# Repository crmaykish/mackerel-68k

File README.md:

# Mackerel 68k

Mackerel 68k is a family of homebrew single-board computers built around the Motorola 68000 line of processors plus a from-scratch effort to run **mainline Linux** on each one.

The project works its way up the 68k family one chip at a time, from the 68008 to the 68040. Each new board adds capability: more memory, faster CPUs, an FPU, an MMU, and richer peripherals. But the throughline is software - every Mackerel runs the **latest mainline Linux kernel**, from a tiny NOMMU uClinux shell on the 68008 up to a full MMU + hardware-FPU install on the 68030.

What's in the box, top to bottom:

- **Bespoke hardware** - custom PCBs with programmable logic chips (22V10 GALs on the 68008, Altera CPLDs on the later boards) handling address decoding, DRAM control, and interrupts.
- **A homegrown bootloader** - a small ROM monitor on every board with debug tools (peek, poke, memtest), YMODEM file transfer, and the ability to boot Linux from IDE or SD.
- **Custom toolchains** - bare-metal and Linux (MMU + NOMMU) GCC cross-compilers built with crosstool-ng.
- **Mainline Linux** - kernel port with drivers for the DUART, IDE storage, and Ethernet-over-SPI, booting to a BusyBox userspace.
- **Fully open source** - every schematic, PCB layout, logic file, and line of code is open, and hobbyists around the world have built their own Mackerel boards.

Three discrete boards are running today (68008, 68010, and 68030), with a 68040 system in the works - plus Mackerel-F, an FPGA build that runs a full Mackerel system on a soft 68000 core.

## Links

1. [Hackaday Project Page](https://hackaday.io/project/183861-mackerel-68k-computer)
2. [Mackerel Linux v7.1.x](https://github.com/crmaykish/mackerel-linux/tree/mackerel)
3. [Mackerel uClinux (deprecated)](https://github.com/crmaykish/mackerel-uclinux-20160919)

## Docs

1. [Mackerel-08 Assembly](docs/mackerel-08-board-assembly.md)
2. [How to Compile Code and Programmable Logic](docs/how-to-compile-everything.md)
3. [Building the Mackerel Toolchains](docs/building-the-mackerel-toolchains.md)
4. [Building and Booting Linux on Mackerel](docs/building-linux-for-mackerel.md)
5. [Building and Running Mackerel-F (FPGA)](docs/building-and-running-mackerel-f.md)

## Hardware

### Mackerel-08

Status: Complete

- MC68008 CPU (52-pin PLCC variant)
- 512 KB of Flash ROM, 3.5MB SRAM
- Two serial ports
- SD card support (bitbang SPI)
- Linux 7.1.x NOMMU

Based on the original prototype hardware, this SBC combines the 52-pin PLCC MC68008, a 512KB Flash ROM, up to 3.5MB of SRAM, and a XR68C681 DUART on a single PCB. The DUART exposes two serial ports and three bit-banged SPI headers. One of these headers is currently used with an SD card breakout board to provide bulk storage.

Three 22V10 PLDs are used for address decoding, interrupt mapping, and DTACK generation. An expansion header breaks out address, data, and control lines to allow additional peripherals to be connected directly to the processor bus.

The address space is mapped as follows:

- RAM:    0x000000 - 0x37FFFF (up to 3.5 MB)
- ROM:    0x380000 - 0x3FBFFF (496/512 KB usable)
- DUART:  0x3FC000 - 0x3FDFFF (8KB)
- Exp:    0x3FE000 - 0x3FFFFF (Expansion header, 8KB)

Mackerel-08 uses a 74HC595 shift register to create a BOOT signal for the first eight /AS cycles of the CPU after reset. This BOOT signal is used by the address decoder PLD to map the ROM to address 0x000000 long enough for the CPU to read the initial stack pointer and program counter vectors from ROM. RAM is mapped to 0x000000 after that.

### Mackerel-10

Status: Complete

- MC68000 or MC68010 CPU
- 1 MB of ROM, 1 MB of SRAM
- Up to 16 MB of 30-pin DRAM (15 usable)
- Two serial ports
- IDE interface
- Linux 7.1.x NOMMU

Mackerel-10 is the second SBC in the project. It expands on the design of Mackerel-08 with a MC68010 CPU (or equivalent), the same XR68C681 DUART, 1MB of Flash ROM, 1MB of SRAM, up to 16 MB of DRAM, and an IDE drive interface. Two CPLDs act as the glue logic and DRAM controller for the board. The SRAM is optional and the address space can be filled almost entirely with DRAM.

The memory map looks like this:

- DRAM:     0x000000 - 0xDFFFFF (14MB)
- SRAM:     0xE00000 - 0xEFFFFF (1 MB)
- ROM:      0xF00000 - 0xFF4000 (not quite 1MB)
- I/O:      0xF40000 - 0xFFFFFF

It's also possible to install a MC68SEC000 CPU on [an adapter](https://github.com/crmaykish/adapters-and-breakout-boards/tree/main/MC68SEC000-to-DIP-64) for a major speed boost. This CPU can run at 33 MHz with the correct CPU oscillator installed and an updated system controller CPLD.

### Mackerel-30

Status: Prototype

- MC68030 CPU at 20 MHz
- MC68882 FPU
- 512 KB ROM, 512 KB SRAM
- 128 MB of 72-pin DRAM
- Two serial ports
- IDE interface
- Ethernet over SPI
- Linux 7.1.x

Mackerel-30 is based on the 68030 CPU. It includes the DUART and IDE interface from Mackerel-10 and upgrades the DRAM controller to use a 72-pin SIMM. It also includes a MC68882 FPU.

### Mackerel-40
Status: Design

- 68040 CPU at 33 MHz (internal MMU and FPU)
- 2 MB of ROM, 2 MB SRAM
- 2x72 pin SIMMs (up to 256 MB of DRAM)
- Dedicated I/O controller (SPI, I2C, GPIO)
- DUART and IDE from earlier boards

### Mackerel-F

Status: Prototype (FPGA)

- fx68k soft 68000 core at 37.8 MHz, in a Tang Nano 20k
- 8 MB SDRAM
- 30 KB ROM (bootloader) and 32 KB BSRAM
- UART console, programmable timer, and interrupt controller
- microSD (SPI) and W5500 Ethernet
- Linux 7.1.x NOMMU

Mackerel-F is an entire Mackerel system implemented inside an FPGA. Everything that is discrete hardware on the other boards - the CPU, glue logic, memory controller, UART, timer, interrupt controller, and SPI masters - is RTL here, built around the [fx68k](https://github.com/ijor/fx68k) soft 68000 core and synthesized for the Tang Nano 20k. The SoC runs at 75.6 MHz with the 68000 core clocked at half that (37.8 MHz).

Unlike the other boards there is no separate ROM chip: the bootloader is baked into the FPGA bitstream as on-chip ROM and its scratch RAM lives in block RAM, so the entire 8 MB of SDRAM is free for Linux. Alongside the usual `boot` (from SD) and YMODEM transfer, the bootloader adds a `netboot` command that pulls the kernel over Ethernet (raw TCP, with a small host server) and a five-second SD autoboot.

The memory map:

- RAM:    0x000000 - 0x7FFFFF (8 MB SDRAM, the top 384 KB holds the execute-in-place root filesystem)
- BSRAM:  0xFF0000 - 0xFF7FFF (32 KB, bootloader RAM)
- ROM:    0xFF8000 - 0xFFF7FF (30 KB, bootloader ROM)
- I/O:    0xFFF800 - 0xFFFFFF (GPIO, UART, timer, two SPI masters, interrupt controller)

It boots mainline NOMMU uClinux to a BusyBox shell from a ROMfs root run in place from SDRAM, with the microSD for storage and the W5500 for networking. See [Building and Running Mackerel-F (FPGA)](docs/building-and-running-mackerel-f.md).

## Software

### Bootloader and Bare-metal Programs
Every version of Mackerel runs a small bootloader program installed on the Flash ROM. This provides a simple set of debugging tools (peek, poke, memtest, etc.) as well as two methods for loading external code.

The bootloader supports the YMODEM protocol for loading programs and data into RAM (see the `ymodem` command), using `lrzsz-sb` on the PC for example. Other terminal programs like TeraTerm should also work.

The `boot` command is used to load the Linux kernel from disk (SD or IDE). It expects a `IMAGE.BIN` file on the first FAT16 partition of the drive. See the `prepare_disk.sh` script in the [mackerel-linux repository](https://github.com/crmaykish/mackerel-linux).

On Mackerel-F the bootloader also supports `netboot` (pulling the kernel over Ethernet) and a five-second SD autoboot on power-up.

### Linux on Mackerel

Every Mackerel board runs the latest mainline kernel (v7.1.x). Mackerel-08, Mackerel-10, and the FPGA-based Mackerel-F run NOMMU and are more limited in their capabilities. Mackerel-30 supports the MMU and the external FPU in Linux and functions more like a traditional headless Linux install. Userspace is made up of busybox (init and shell) with driver support for the DUART, IDE storage, and networking over SPI.

### Compilers and Tools
There are three different toolchains for Mackerel. The baremetal toolchain builds the bootloader and other low level programs in this repo. There are also two variants of the Linux toolchain - one for Mackerel-30 with MMU support and the other for NOMMU/ucLinux on Mackerel-08/10. Prebuilt toolchains are available on the [releases page](https://github.com/crmaykish/mackerel-68k/releases/tag/toolchains-2026-06-06); see [Building the Mackerel Toolchains](docs/building-the-mackerel-toolchains.md) for both the download steps and instructions on building them all with crosstools-ng.

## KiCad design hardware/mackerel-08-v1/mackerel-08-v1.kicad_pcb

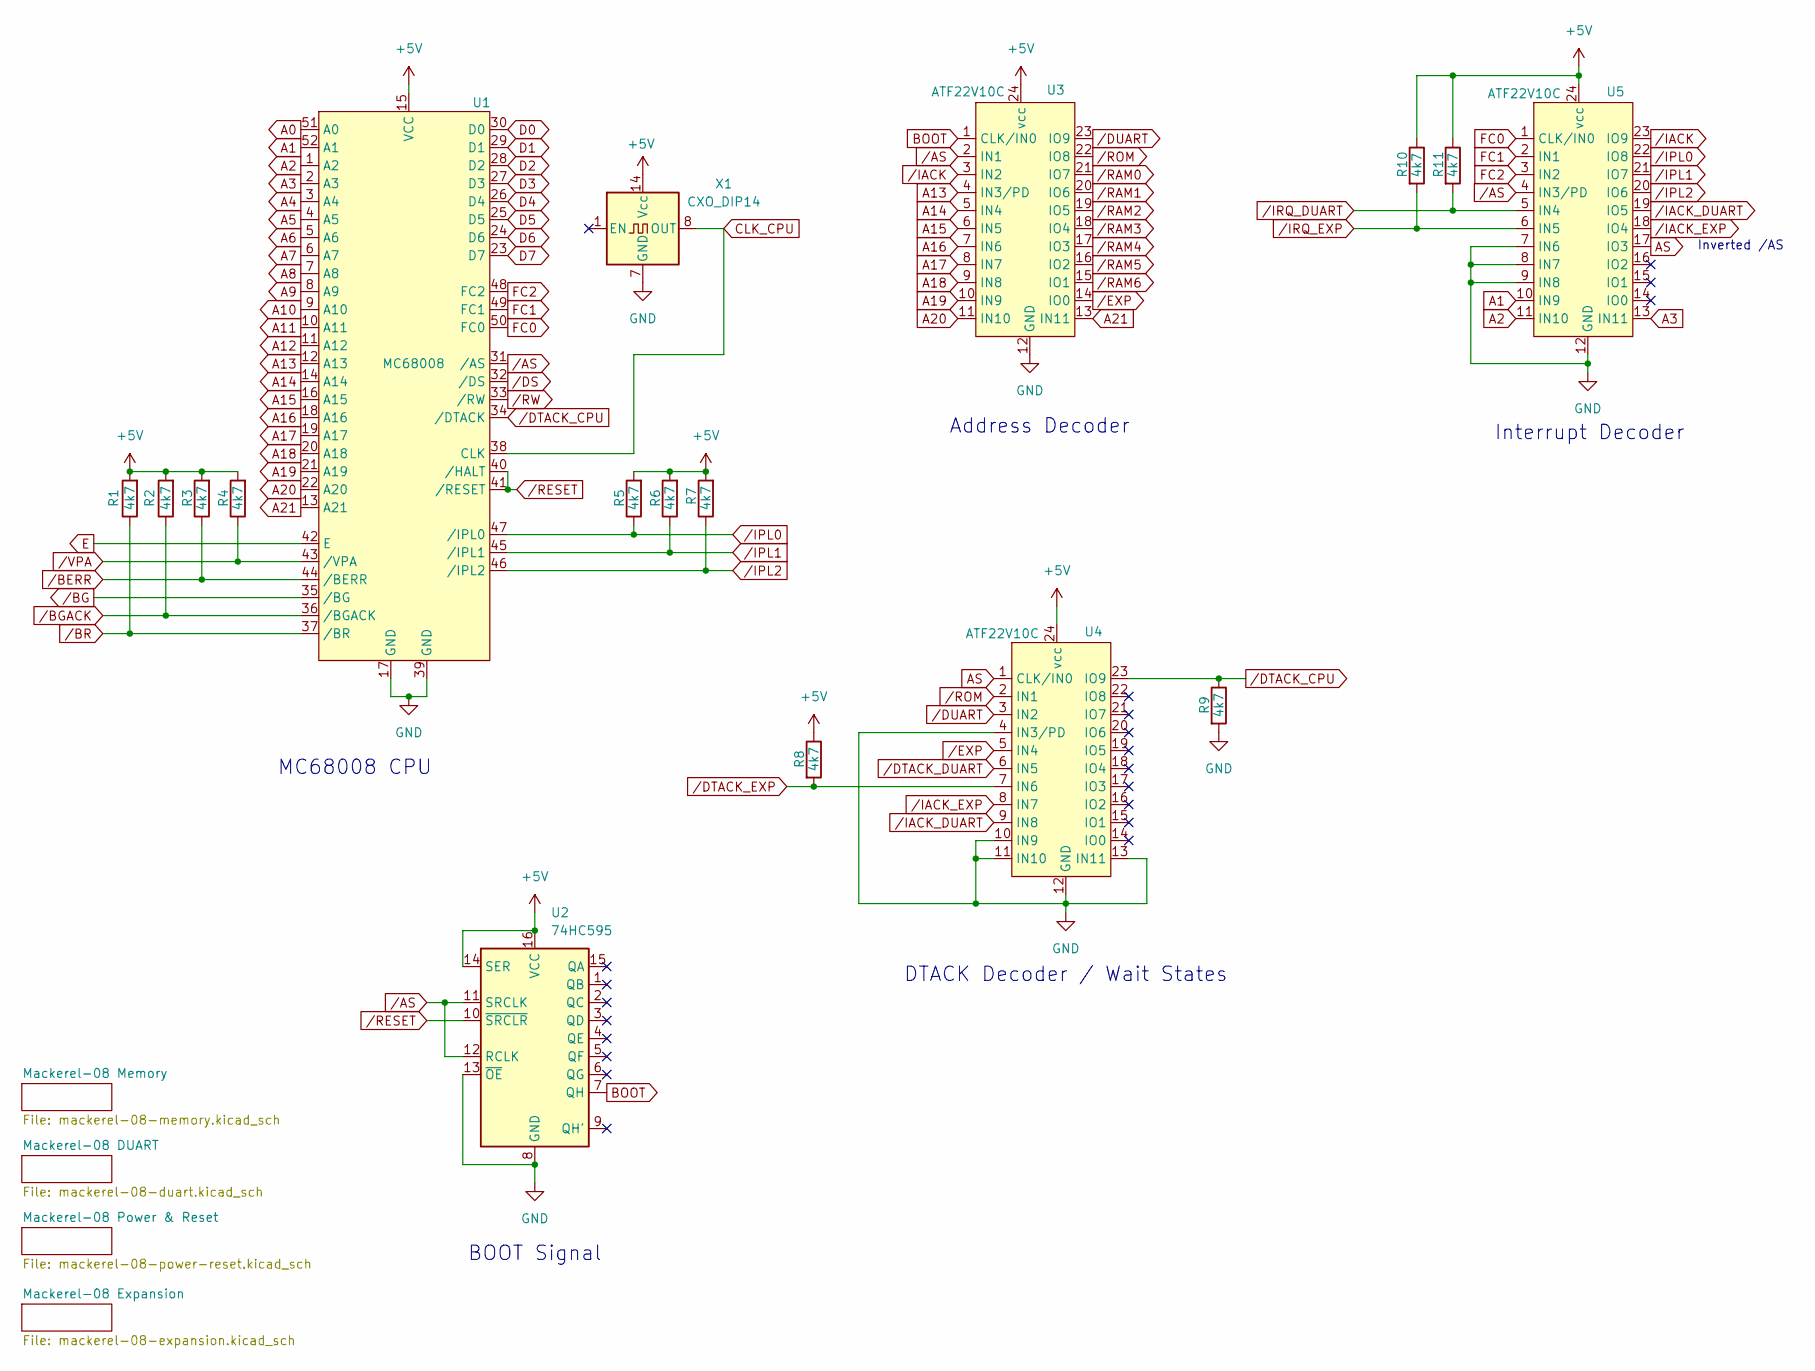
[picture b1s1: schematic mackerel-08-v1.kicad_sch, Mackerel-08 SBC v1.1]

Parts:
R1, R2, R3, R4, R5, R6, R7, R8, R9, R10, R11: 4k7; R_1206_3216Metric_Pad1.30x1.75mm_HandSolder
U1: MC68008; PLCC-52_THT-Socket
U2: 74HC595; DIP-16_W7.62mm
U3, U4, U5: ATF22V10C; DIP-24_W7.62mm
X1: CXO_DIP14; Oscillator_DIP-14

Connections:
+5V: R1.2, R2.2, R3.2, R4.2, R5.2, R6.2, R7.2, R8.1, R10.1, R11.1, U1.15 (VCC), U2.14 (SER), U2.16 (VCC), U3.24 (vcc), U4.24 (vcc), U5.24 (vcc), X1.14 (Vcc); also elsewhere on the board
A0: U1.51 (A0); also elsewhere on the board
A1: U1.52 (A1), U5.10 (IN9); also elsewhere on the board
A2: U1.1 (A2), U5.11 (IN10); also elsewhere on the board
A3: U1.2 (A3), U5.13 (IN11); also elsewhere on the board
A4: U1.3 (A4); also elsewhere on the board
A5: U1.4 (A5); also elsewhere on the board
A6: U1.5 (A6); also elsewhere on the board
A7: U1.6 (A7); also elsewhere on the board
A8: U1.7 (A8); also elsewhere on the board
A9: U1.8 (A9); also elsewhere on the board
A10: U1.9 (A10); also elsewhere on the board
A11: U1.10 (A11); also elsewhere on the board
A12: U1.11 (A12); also elsewhere on the board
A13: U1.12 (A13), U3.4 (IN3/PD); also elsewhere on the board
A14: U1.14 (A14), U3.5 (IN4); also elsewhere on the board
A15: U1.16 (A15), U3.6 (IN5); also elsewhere on the board
A16: U1.18 (A16), U3.7 (IN6); also elsewhere on the board
A17: U1.19 (A17), U3.8 (IN7); also elsewhere on the board
A18: U1.20 (A18), U3.9 (IN8); also elsewhere on the board
A19: U1.21 (A19), U3.10 (IN9); also elsewhere on the board
A20: U1.22 (A20), U3.11 (IN10); also elsewhere on the board
A21: U1.13 (A21), U3.13 (IN11); also elsewhere on the board
AS: U4.1 (CLK/IN0), U5.17 (IO3)
BOOT: U2.7 (QH), U3.1 (CLK/IN0)
CLK_CPU: U1.38 (CLK), X1.8 (OUT); also elsewhere on the board
D0: U1.30 (D0); also elsewhere on the board
D1: U1.29 (D1); also elsewhere on the board
D2: U1.28 (D2); also elsewhere on the board
D3: U1.27 (D3); also elsewhere on the board
D4: U1.26 (D4); also elsewhere on the board
D5: U1.25 (D5); also elsewhere on the board
D6: U1.24 (D6); also elsewhere on the board
D7: U1.23 (D7); also elsewhere on the board
E: U1.42 (E); also elsewhere on the board
FC0: U1.50 (FC0), U5.1 (CLK/IN0)
FC1: U1.49 (FC1), U5.2 (IN1)
FC2: U1.48 (FC2), U5.3 (IN2)
GND: R9.2, U1.17 (GND), U1.39 (GND), U2.8 (GND), U2.13 (~OE), U3.12 (GND), U4.4 (IN3/PD), U4.10 (IN9), U4.11 (IN10), U4.12 (GND), U4.13 (IN11), U5.7 (IN6), U5.8 (IN7), U5.9 (IN8), U5.12 (GND), X1.7 (GND); also elsewhere on the board
/AS: U1.31 (/AS), U2.11 (SRCLK), U2.12 (RCLK), U3.2 (IN1), U5.4 (IN3/PD); also elsewhere on the board
/BERR: R3.1, U1.44 (/BERR); also elsewhere on the board
/BG: U1.35 (/BG); also elsewhere on the board
/BGACK: R2.1, U1.36 (/BGACK); also elsewhere on the board
/BR: R1.1, U1.37 (/BR); also elsewhere on the board
/DS: U1.32 (/DS); also elsewhere on the board
/DTACK_CPU: R9.1, U1.34 (/DTACK), U4.23 (IO9)
/DTACK_DUART: U4.6 (IN5); also elsewhere on the board
/DTACK_EXP: R8.2, U4.7 (IN6); also elsewhere on the board
/DUART: U3.23 (IO9), U4.3 (IN2); also elsewhere on the board
/EXP: U3.14 (IO0), U4.5 (IN4); also elsewhere on the board
/IACK: U3.3 (IN2), U5.23 (IO9)
/IACK_DUART: U4.9 (IN8), U5.19 (IO5); also elsewhere on the board
/IACK_EXP: U4.8 (IN7), U5.18 (IO4); also elsewhere on the board
/IPL0: R5.1, U1.47 (/IPL0), U5.22 (IO8)
/IPL1: R6.1, U1.45 (/IPL1), U5.21 (IO7)
/IPL2: R7.1, U1.46 (/IPL2), U5.20 (IO6)
/IRQ_DUART: R11.2, U5.5 (IN4); also elsewhere on the board
/IRQ_EXP: R10.2, U5.6 (IN5); also elsewhere on the board
/RAM0: U3.21 (IO7); also elsewhere on the board
/RAM1: U3.20 (IO6); also elsewhere on the board
/RAM2: U3.19 (IO5); also elsewhere on the board
/RAM3: U3.18 (IO4); also elsewhere on the board
/RAM4: U3.17 (IO3); also elsewhere on the board
/RAM5: U3.16 (IO2); also elsewhere on the board
/RAM6: U3.15 (IO1); also elsewhere on the board
/RESET: U1.40 (/HALT), U1.41 (/RESET), U2.10 (~SRCLR); also elsewhere on the board
/ROM: U3.22 (IO8), U4.2 (IN1); also elsewhere on the board
/RW: U1.33 (/RW); also elsewhere on the board
/VPA: R4.1, U1.43 (/VPA); also elsewhere on the board

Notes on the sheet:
DTACK Decoder / Wait States
MC68008 CPU
Inverted /AS
BOOT Signal
Interrupt Decoder
Address Decoder

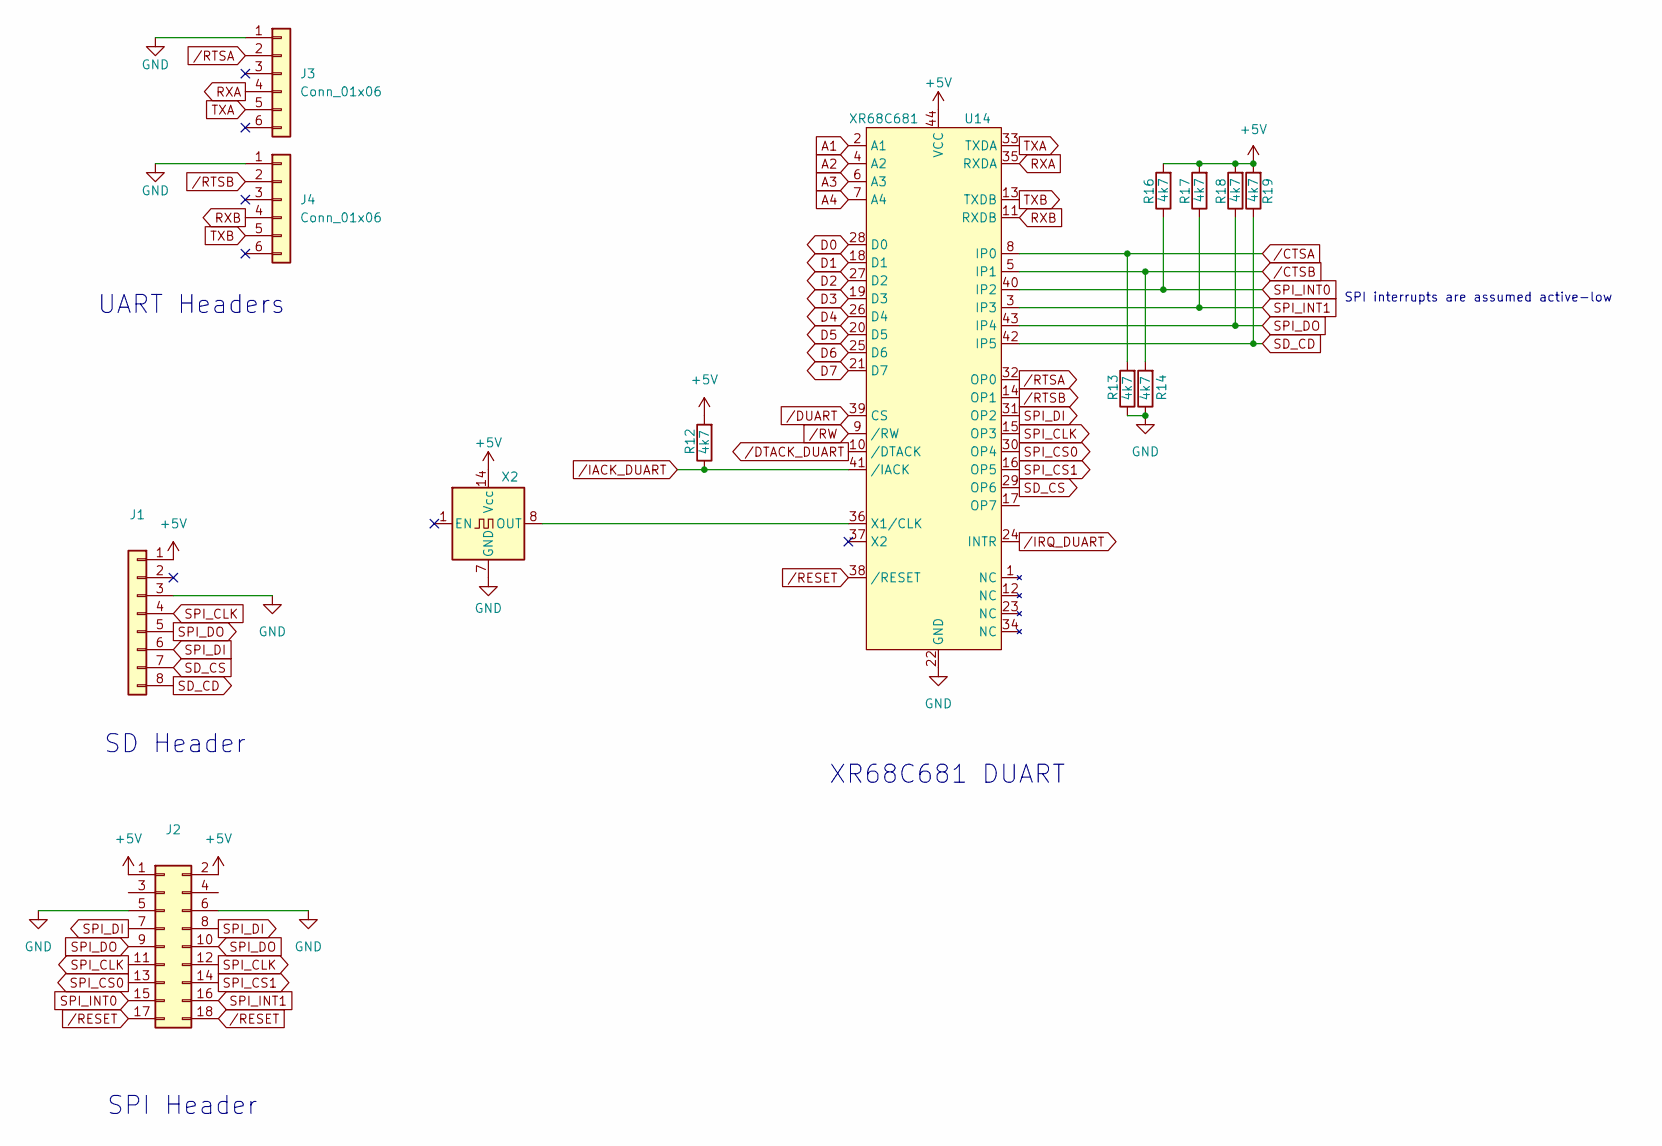
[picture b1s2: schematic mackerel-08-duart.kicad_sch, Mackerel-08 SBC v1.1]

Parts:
J1: Conn_01x08; PinSocket_1x08_P2.54mm_Vertical
J2: Conn_02x09_Odd_Even; PinHeader_2x09_P2.54mm_Vertical
J3, J4: Conn_01x06; PinSocket_1x06_P2.54mm_Horizontal
R12, R13, R14, R16, R17, R18, R19: 4k7; R_1206_3216Metric_Pad1.30x1.75mm_HandSolder
U14: XR68C681; PLCC-44_THT-Socket
X2: CXO_DIP14; Oscillator_DIP-14

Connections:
+5V: J1.1, J2.1, J2.2, R12.2, R16.2, R17.2, R18.2, R19.2, U14.44 (VCC), X2.14 (Vcc); also elsewhere on the board
/Mackerel-08 DUART/USR_LED: U14.17 (OP7); also elsewhere on the board
A1: U14.2 (A1); also elsewhere on the board
A2: U14.4 (A2); also elsewhere on the board
A3: U14.6 (A3); also elsewhere on the board
A4: U14.7 (A4); also elsewhere on the board
D0: U14.28 (D0); also elsewhere on the board
D1: U14.18 (D1); also elsewhere on the board
D2: U14.27 (D2); also elsewhere on the board
D3: U14.19 (D3); also elsewhere on the board
D4: U14.26 (D4); also elsewhere on the board
D5: U14.20 (D5); also elsewhere on the board
D6: U14.25 (D6); also elsewhere on the board
D7: U14.21 (D7); also elsewhere on the board
GND: J1.3, J2.5, J2.6, J3.1, J4.1, R13.1, R14.1, U14.22 (GND), X2.7 (GND); also elsewhere on the board
unnamed: U14.36 (X1/CLK), X2.8 (OUT)
RXA: J3.4, U14.35 (RXDA)
RXB: J4.4, U14.11 (RXDB)
SD_CD: J1.8, R19.1, U14.42 (IP5)
SD_CS: J1.7, U14.29 (OP6)
SPI_CLK: J1.4, J2.11, J2.12, U14.15 (OP3)
SPI_CS0: J2.13, U14.30 (OP4)
SPI_CS1: J2.14, U14.16 (OP5)
SPI_DI: J1.6, J2.7, J2.8, U14.31 (OP2)
SPI_DO: J1.5, J2.9, J2.10, R18.1, U14.43 (IP4)
SPI_INT0: J2.15, R16.1, U14.40 (IP2)
SPI_INT1: J2.16, R17.1, U14.3 (IP3)
TXA: J3.5, U14.33 (TXDA)
TXB: J4.5, U14.13 (TXDB)
/CTSA: R13.2, U14.8 (IP0)
/CTSB: R14.2, U14.5 (IP1)
/DTACK_DUART: U14.10 (/DTACK); also elsewhere on the board
/DUART: U14.39 (CS); also elsewhere on the board
/IACK_DUART: R12.1, U14.41 (/IACK); also elsewhere on the board
/IRQ_DUART: U14.24 (INTR); also elsewhere on the board
/RESET: J2.17, J2.18, U14.38 (/RESET); also elsewhere on the board
/RTSA: J3.2, U14.32 (OP0)
/RTSB: J4.2, U14.14 (OP1)
/RW: U14.9 (/RW); also elsewhere on the board

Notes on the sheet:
SPI interrupts are assumed active-low
XR68C681 DUART
SPI Header
UART Headers
SD Header

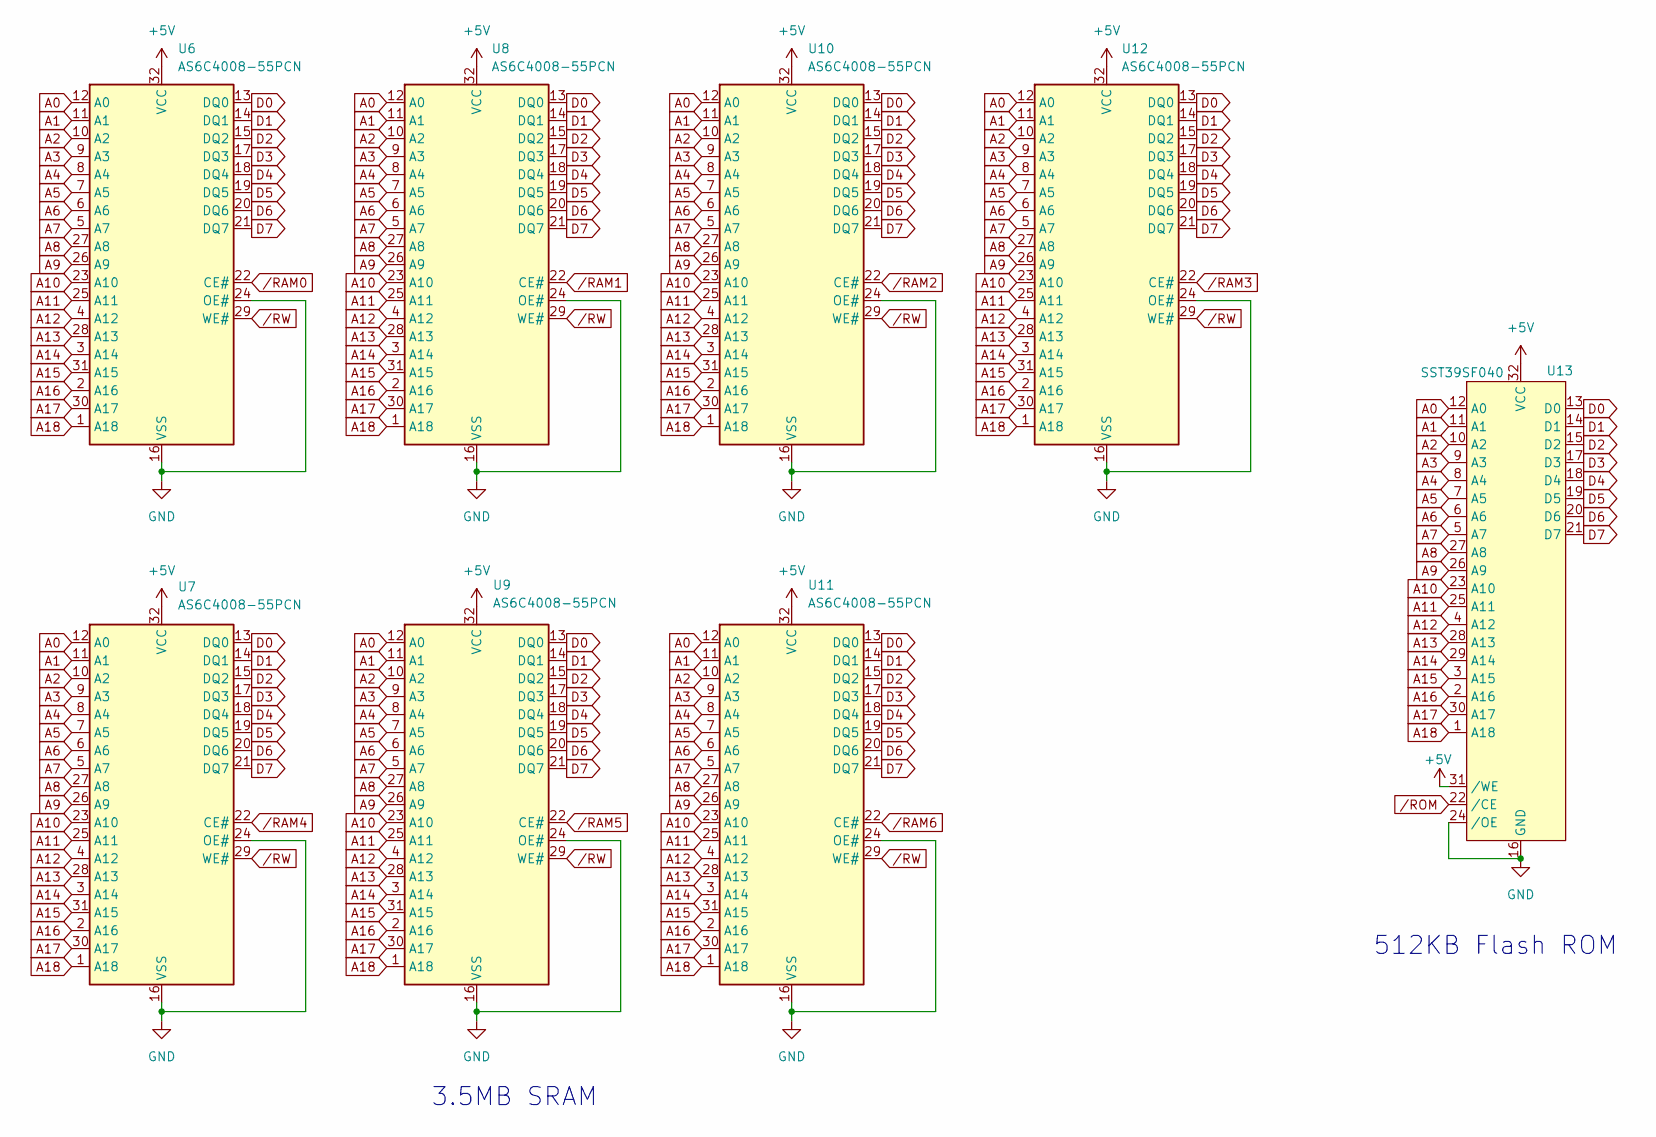
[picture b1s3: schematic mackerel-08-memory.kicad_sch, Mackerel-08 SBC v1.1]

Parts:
U6, U7, U8, U9, U10, U11, U12: AS6C4008-55PCN; DIP-32_W15.24mm
U13: SST39SF040; DIP_Socket-32_W11.9_W12.7_W15.24_W17.78_W18.5_3M_232-1285-0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

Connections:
+5V: U6.32 (VCC), U7.32 (VCC), U8.32 (VCC), U9.32 (VCC), U10.32 (VCC), U11.32 (VCC), U12.32 (VCC), U13.31 (/WE), U13.32 (VCC); also elsewhere on the board
A0: U6.12 (A0), U7.12 (A0), U8.12 (A0), U9.12 (A0), U10.12 (A0), U11.12 (A0), U12.12 (A0), U13.12 (A0); also elsewhere on the board
A1: U6.11 (A1), U7.11 (A1), U8.11 (A1), U9.11 (A1), U10.11 (A1), U11.11 (A1), U12.11 (A1), U13.11 (A1); also elsewhere on the board
A2: U6.10 (A2), U7.10 (A2), U8.10 (A2), U9.10 (A2), U10.10 (A2), U11.10 (A2), U12.10 (A2), U13.10 (A2); also elsewhere on the board
A3: U6.9 (A3), U7.9 (A3), U8.9 (A3), U9.9 (A3), U10.9 (A3), U11.9 (A3), U12.9 (A3), U13.9 (A3); also elsewhere on the board
A4: U6.8 (A4), U7.8 (A4), U8.8 (A4), U9.8 (A4), U10.8 (A4), U11.8 (A4), U12.8 (A4), U13.8 (A4); also elsewhere on the board
A5: U6.7 (A5), U7.7 (A5), U8.7 (A5), U9.7 (A5), U10.7 (A5), U11.7 (A5), U12.7 (A5), U13.7 (A5); also elsewhere on the board
A6: U6.6 (A6), U7.6 (A6), U8.6 (A6), U9.6 (A6), U10.6 (A6), U11.6 (A6), U12.6 (A6), U13.6 (A6); also elsewhere on the board
A7: U6.5 (A7), U7.5 (A7), U8.5 (A7), U9.5 (A7), U10.5 (A7), U11.5 (A7), U12.5 (A7), U13.5 (A7); also elsewhere on the board
A8: U6.27 (A8), U7.27 (A8), U8.27 (A8), U9.27 (A8), U10.27 (A8), U11.27 (A8), U12.27 (A8), U13.27 (A8); also elsewhere on the board
A9: U6.26 (A9), U7.26 (A9), U8.26 (A9), U9.26 (A9), U10.26 (A9), U11.26 (A9), U12.26 (A9), U13.26 (A9); also elsewhere on the board
A10: U6.23 (A10), U7.23 (A10), U8.23 (A10), U9.23 (A10), U10.23 (A10), U11.23 (A10), U12.23 (A10), U13.23 (A10); also elsewhere on the board
A11: U6.25 (A11), U7.25 (A11), U8.25 (A11), U9.25 (A11), U10.25 (A11), U11.25 (A11), U12.25 (A11), U13.25 (A11); also elsewhere on the board
A12: U6.4 (A12), U7.4 (A12), U8.4 (A12), U9.4 (A12), U10.4 (A12), U11.4 (A12), U12.4 (A12), U13.4 (A12); also elsewhere on the board
A13: U6.28 (A13), U7.28 (A13), U8.28 (A13), U9.28 (A13), U10.28 (A13), U11.28 (A13), U12.28 (A13), U13.28 (A13); also elsewhere on the board
A14: U6.3 (A14), U7.3 (A14), U8.3 (A14), U9.3 (A14), U10.3 (A14), U11.3 (A14), U12.3 (A14), U13.29 (A14); also elsewhere on the board
A15: U6.31 (A15), U7.31 (A15), U8.31 (A15), U9.31 (A15), U10.31 (A15), U11.31 (A15), U12.31 (A15), U13.3 (A15); also elsewhere on the board
A16: U6.2 (A16), U7.2 (A16), U8.2 (A16), U9.2 (A16), U10.2 (A16), U11.2 (A16), U12.2 (A16), U13.2 (A16); also elsewhere on the board
A17: U6.30 (A17), U7.30 (A17), U8.30 (A17), U9.30 (A17), U10.30 (A17), U11.30 (A17), U12.30 (A17), U13.30 (A17); also elsewhere on the board
A18: U6.1 (A18), U7.1 (A18), U8.1 (A18), U9.1 (A18), U10.1 (A18), U11.1 (A18), U12.1 (A18), U13.1 (A18); also elsewhere on the board
D0: U6.13 (DQ0), U7.13 (DQ0), U8.13 (DQ0), U9.13 (DQ0), U10.13 (DQ0), U11.13 (DQ0), U12.13 (DQ0), U13.13 (D0); also elsewhere on the board
D1: U6.14 (DQ1), U7.14 (DQ1), U8.14 (DQ1), U9.14 (DQ1), U10.14 (DQ1), U11.14 (DQ1), U12.14 (DQ1), U13.14 (D1); also elsewhere on the board
D2: U6.15 (DQ2), U7.15 (DQ2), U8.15 (DQ2), U9.15 (DQ2), U10.15 (DQ2), U11.15 (DQ2), U12.15 (DQ2), U13.15 (D2); also elsewhere on the board
D3: U6.17 (DQ3), U7.17 (DQ3), U8.17 (DQ3), U9.17 (DQ3), U10.17 (DQ3), U11.17 (DQ3), U12.17 (DQ3), U13.17 (D3); also elsewhere on the board
D4: U6.18 (DQ4), U7.18 (DQ4), U8.18 (DQ4), U9.18 (DQ4), U10.18 (DQ4), U11.18 (DQ4), U12.18 (DQ4), U13.18 (D4); also elsewhere on the board
D5: U6.19 (DQ5), U7.19 (DQ5), U8.19 (DQ5), U9.19 (DQ5), U10.19 (DQ5), U11.19 (DQ5), U12.19 (DQ5), U13.19 (D5); also elsewhere on the board
D6: U6.20 (DQ6), U7.20 (DQ6), U8.20 (DQ6), U9.20 (DQ6), U10.20 (DQ6), U11.20 (DQ6), U12.20 (DQ6), U13.20 (D6); also elsewhere on the board
D7: U6.21 (DQ7), U7.21 (DQ7), U8.21 (DQ7), U9.21 (DQ7), U10.21 (DQ7), U11.21 (DQ7), U12.21 (DQ7), U13.21 (D7); also elsewhere on the board
GND: U6.16 (VSS), U6.24 (OE#), U7.16 (VSS), U7.24 (OE#), U8.16 (VSS), U8.24 (OE#), U9.16 (VSS), U9.24 (OE#), U10.16 (VSS), U10.24 (OE#), U11.16 (VSS), U11.24 (OE#), U12.16 (VSS), U12.24 (OE#), U13.16 (GND), U13.24 (/OE); also elsewhere on the board
/RAM0: U6.22 (CE#); also elsewhere on the board
/RAM1: U8.22 (CE#); also elsewhere on the board
/RAM2: U10.22 (CE#); also elsewhere on the board
/RAM3: U12.22 (CE#); also elsewhere on the board
/RAM4: U7.22 (CE#); also elsewhere on the board
/RAM5: U9.22 (CE#); also elsewhere on the board
/RAM6: U11.22 (CE#); also elsewhere on the board
/ROM: U13.22 (/CE); also elsewhere on the board
/RW: U6.29 (WE#), U7.29 (WE#), U8.29 (WE#), U9.29 (WE#), U10.29 (WE#), U11.29 (WE#), U12.29 (WE#); also elsewhere on the board

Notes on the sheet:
512KB Flash ROM
3.5MB SRAM

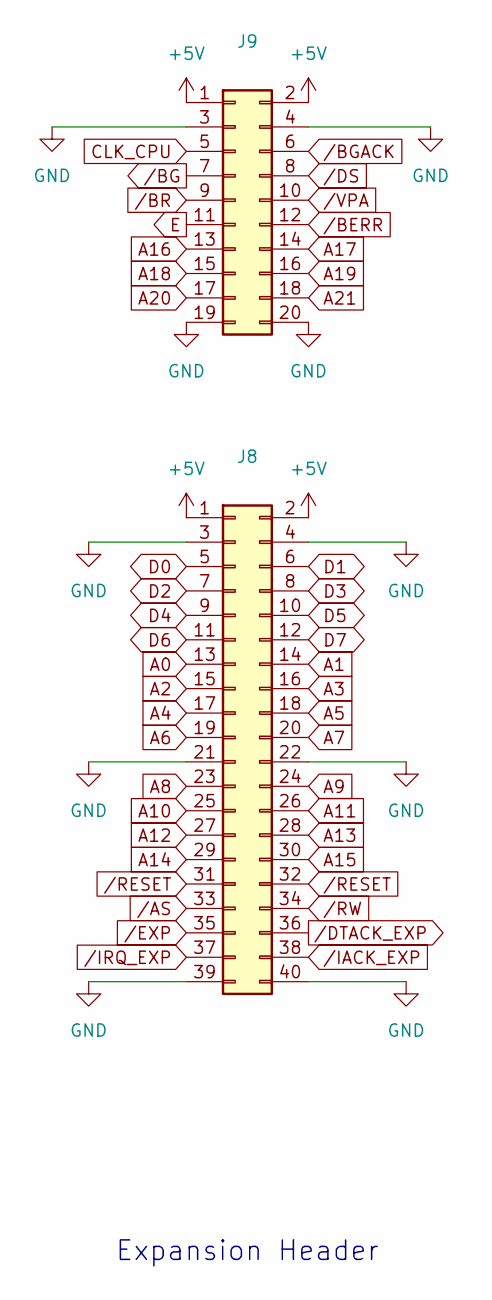
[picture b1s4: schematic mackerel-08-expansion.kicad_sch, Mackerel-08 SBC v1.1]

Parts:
J8: Conn_02x20_Odd_Even; IDC-Header_2x20_P2.54mm_Vertical
J9: Conn_02x10_Odd_Even; IDC-Header_2x10_P2.54mm_Vertical

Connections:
+5V: J8.1, J8.2, J9.1, J9.2; also elsewhere on the board
A0: J8.13; also elsewhere on the board
A1: J8.14; also elsewhere on the board
A2: J8.15; also elsewhere on the board
A3: J8.16; also elsewhere on the board
A4: J8.17; also elsewhere on the board
A5: J8.18; also elsewhere on the board
A6: J8.19; also elsewhere on the board
A7: J8.20; also elsewhere on the board
A8: J8.23; also elsewhere on the board
A9: J8.24; also elsewhere on the board
A10: J8.25; also elsewhere on the board
A11: J8.26; also elsewhere on the board
A12: J8.27; also elsewhere on the board
A13: J8.28; also elsewhere on the board
A14: J8.29; also elsewhere on the board
A15: J8.30; also elsewhere on the board
A16: J9.13; also elsewhere on the board
A17: J9.14; also elsewhere on the board
A18: J9.15; also elsewhere on the board
A19: J9.16; also elsewhere on the board
A20: J9.17; also elsewhere on the board
A21: J9.18; also elsewhere on the board
CLK_CPU: J9.5; also elsewhere on the board
D0: J8.5; also elsewhere on the board
D1: J8.6; also elsewhere on the board
D2: J8.7; also elsewhere on the board
D3: J8.8; also elsewhere on the board
D4: J8.9; also elsewhere on the board
D5: J8.10; also elsewhere on the board
D6: J8.11; also elsewhere on the board
D7: J8.12; also elsewhere on the board
E: J9.11; also elsewhere on the board
GND: J8.3, J8.4, J8.21, J8.22, J8.39, J8.40, J9.3, J9.4, J9.19, J9.20; also elsewhere on the board
/AS: J8.33; also elsewhere on the board
/BERR: J9.12; also elsewhere on the board
/BG: J9.7; also elsewhere on the board
/BGACK: J9.6; also elsewhere on the board
/BR: J9.9; also elsewhere on the board
/DS: J9.8; also elsewhere on the board
/DTACK_EXP: J8.36; also elsewhere on the board
/EXP: J8.35; also elsewhere on the board
/IACK_EXP: J8.38; also elsewhere on the board
/IRQ_EXP: J8.37; also elsewhere on the board
/RESET: J8.31, J8.32; also elsewhere on the board
/RW: J8.34; also elsewhere on the board
/VPA: J9.10; also elsewhere on the board

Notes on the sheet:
Expansion Header

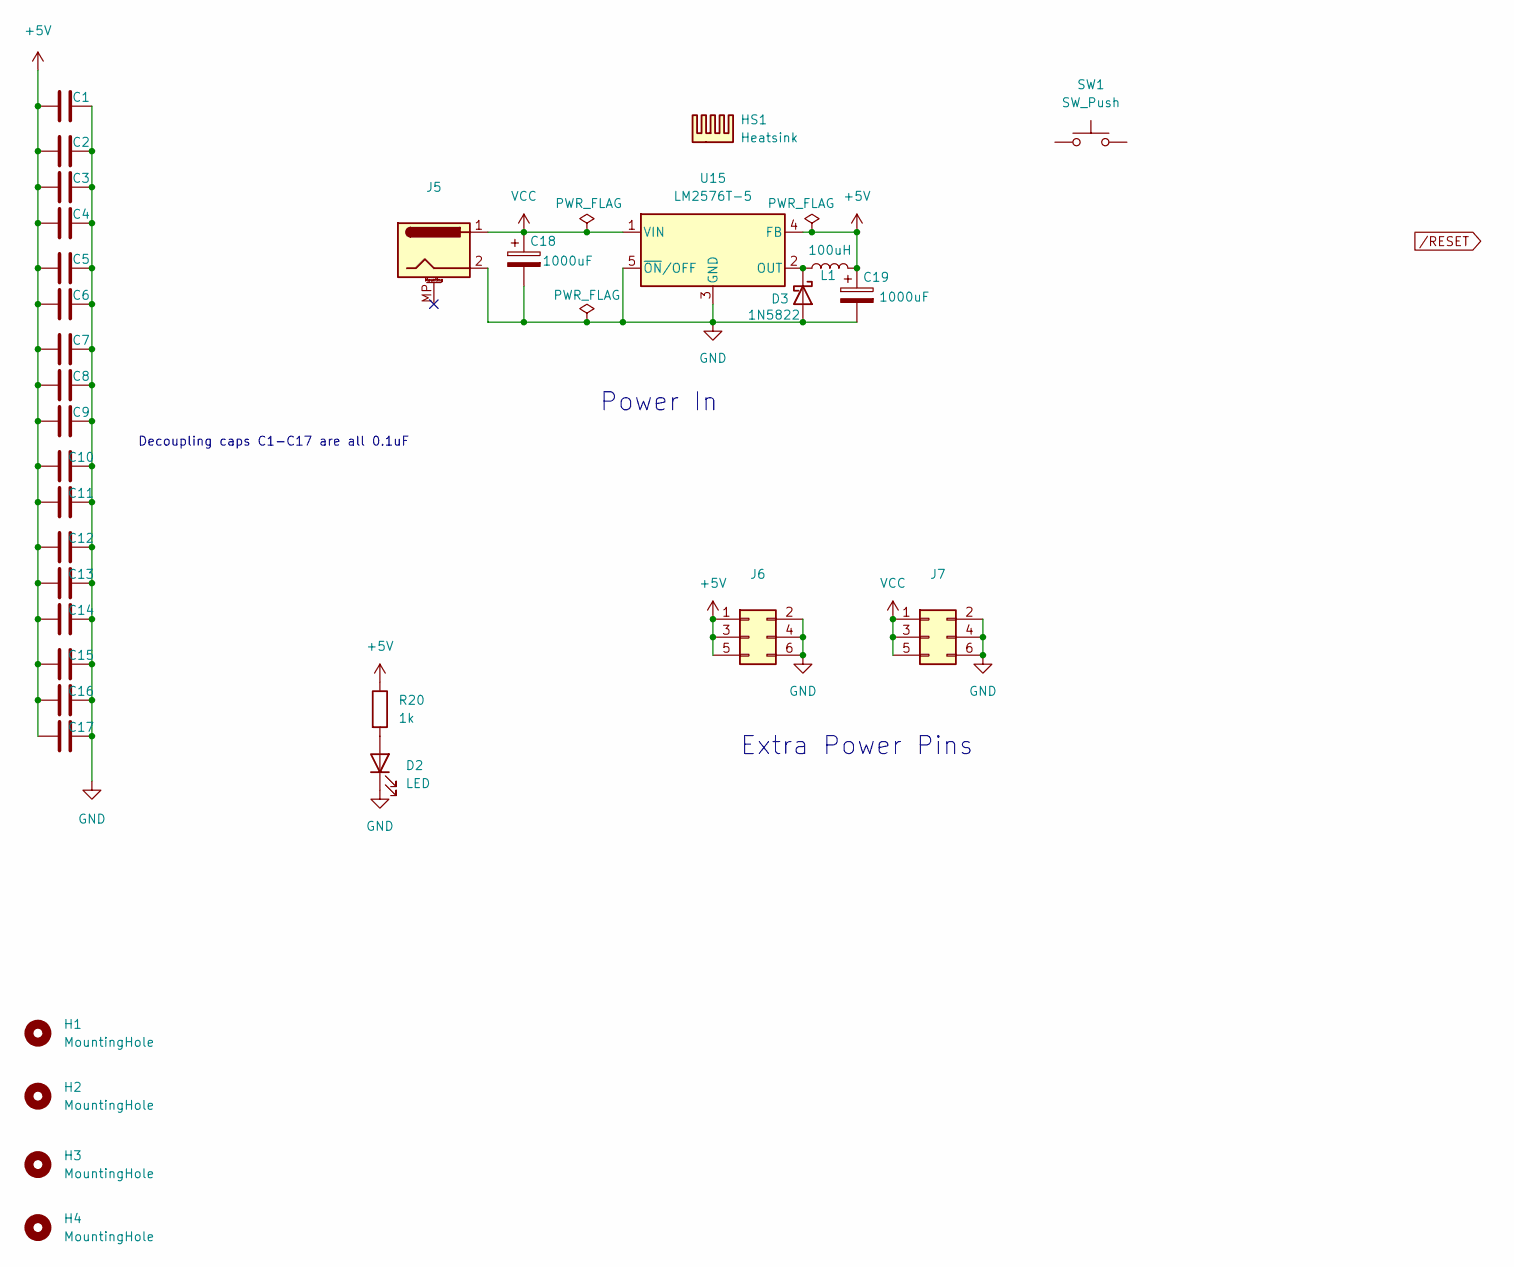
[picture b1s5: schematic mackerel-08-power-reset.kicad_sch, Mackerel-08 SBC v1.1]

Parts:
C1, C2, C3, C4, C5, C6, C7, C8, C9, C10, C11, C12, C13, C14, C15, C16, C17: 0.1uF; C_Disc_D4.3mm_W1.9mm_P5.00mm
C18, C19: 1000uF; CP_Radial_D10.0mm_P5.00mm
D2: LED; LED_D5.0mm
D3: 1N5822; D_DO-27_P15.24mm_Horizontal
H1, H2, H3, H4: MountingHole; MountingHole_3.2mm_M3_Pad
HS1: Heatsink; Heatsink_Stonecold_HS-S02_13.21x9.53mm
J5: Barrel_Jack_MountingPin; BarrelJack_Horizontal
J6, J7: Conn_02x03_Odd_Even; PinHeader_2x03_P2.54mm_Vertical
L1: 100uH; L_Radial_D10.0mm_P5.00mm_Fastron_07M
R20: 1k; R_1206_3216Metric_Pad1.30x1.75mm_HandSolder
SW1: SW_Push; SW_PUSH_6mm_H5mm
U15: LM2576T-5; TO-220-5_Vertical

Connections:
+5V: C1.1, C2.1, C3.1, C4.1, C5.1, C6.1, C7.1, C8.1, C9.1, C10.1, C11.1, C12.1, C13.1, C14.1, C15.1, C16.1, C17.1, C19.1, J6.1, J6.3, J6.5, L1.2, R20.1, U15.4 (FB); also elsewhere on the board
GND: C1.2, C2.2, C3.2, C4.2, C5.2, C6.2, C7.2, C8.2, C9.2, C10.2, C11.2, C12.2, C13.2, C14.2, C15.2, C16.2, C17.2, C18.2, C19.2, D2.1 (K), D3.2 (A), J5.2, J6.2, J6.4, J6.6, J7.2, J7.4, J7.6, U15.3 (GND), U15.5 (~ON/OFF); also elsewhere on the board
unnamed: D2.2 (A), R20.2
unnamed: D3.1 (K), L1.1, U15.2 (OUT)
VCC: C18.1, J5.1, J7.1, J7.3, J7.5, U15.1 (VIN)

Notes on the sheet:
Decoupling caps C1-C17 are all 0.1uF
Power In
Extra Power Pins

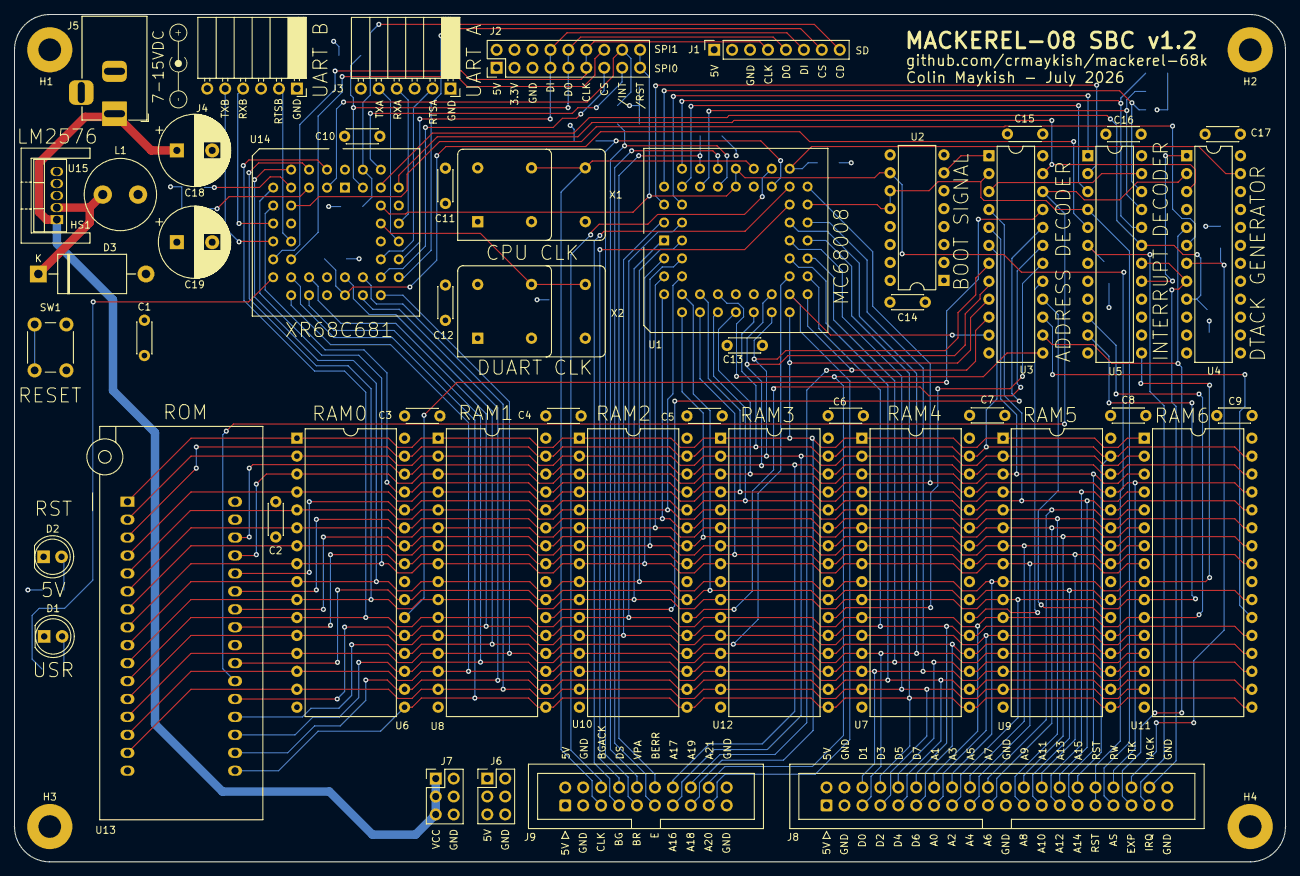
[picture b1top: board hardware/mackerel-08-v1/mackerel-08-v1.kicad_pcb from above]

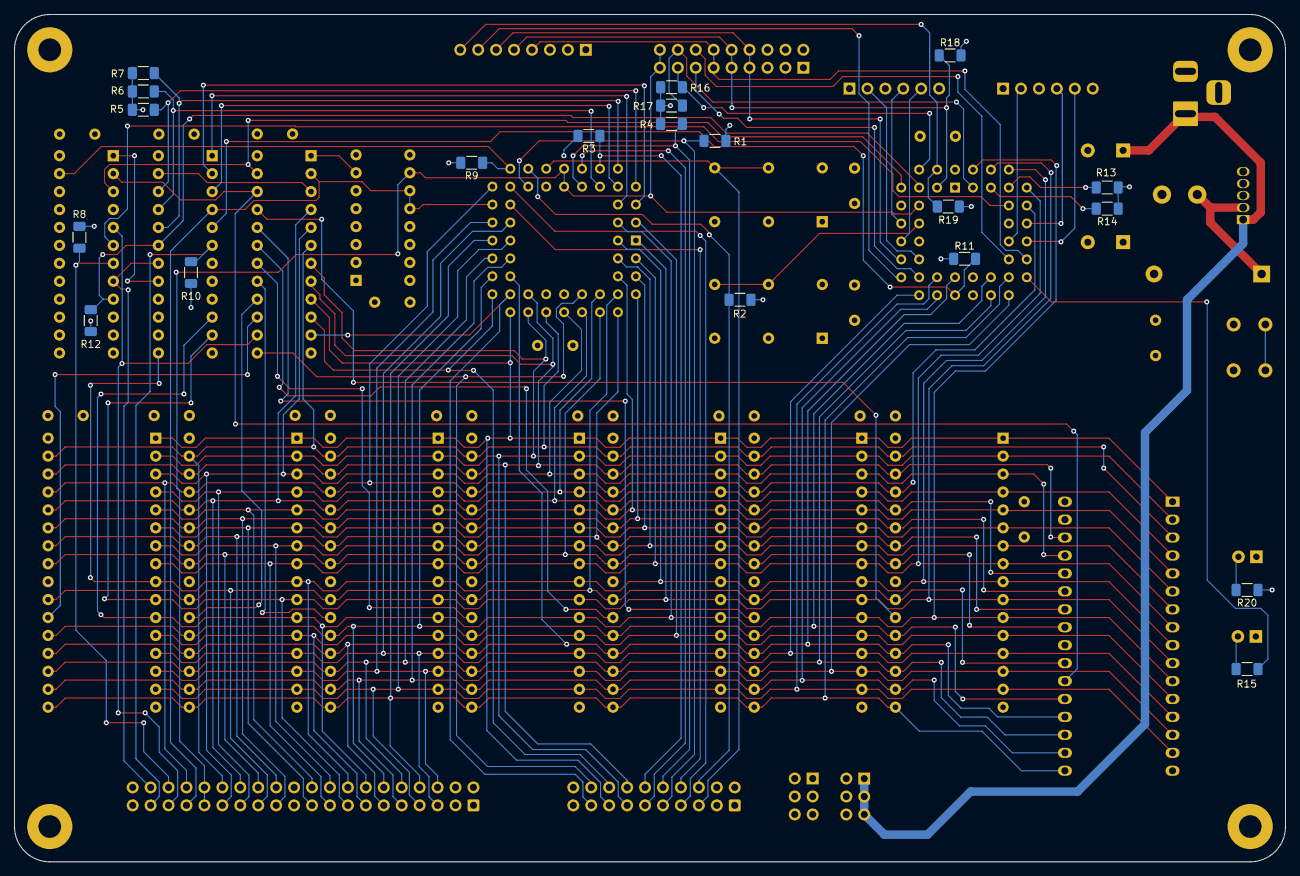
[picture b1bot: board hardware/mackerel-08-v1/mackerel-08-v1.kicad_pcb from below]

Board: 4 copper layers, 180.0 x 120.0 mm, 75 parts (20 on the bottom side), 92 nets.

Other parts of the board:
D1: LED; LED_D5.0mm
R15: 1k; R_1206_3216Metric_Pad1.30x1.75mm_HandSolder

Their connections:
/Mackerel-08 DUART/USR_LED: R15.1; also elsewhere on the board
GND: D1.1 (K); also elsewhere on the board
unnamed: D1.2 (A), R15.2
